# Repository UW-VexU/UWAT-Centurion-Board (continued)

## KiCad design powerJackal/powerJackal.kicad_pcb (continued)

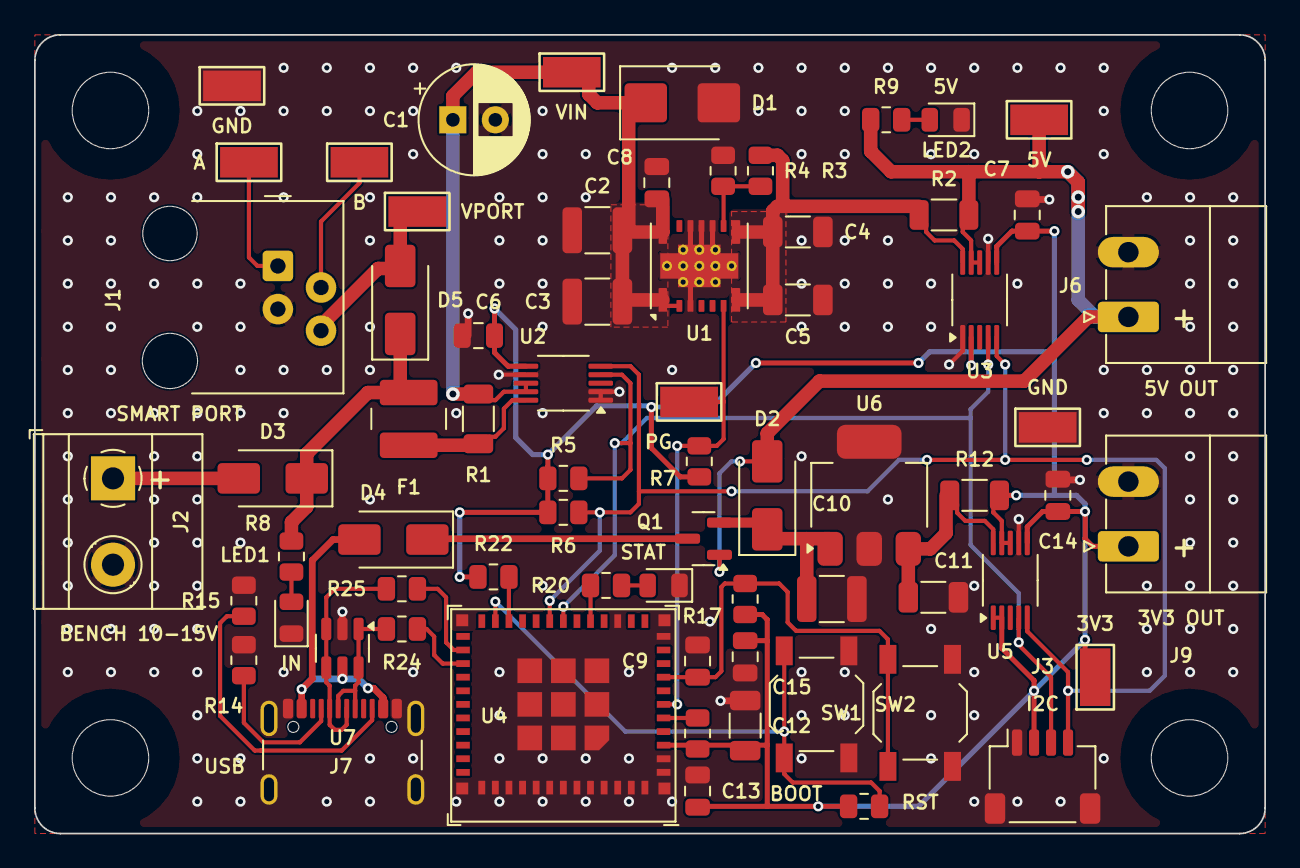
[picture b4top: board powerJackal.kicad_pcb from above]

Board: 2 copper layers, 72.4 x 47.0 mm, 72 parts (0 on the bottom side), 33 nets.

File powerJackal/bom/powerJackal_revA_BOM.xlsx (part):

Smart Port Power Test Board (Jackal), Bill of Materials, Rev A draft 8 (TPSM536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
UWAT VEXU. DigiKey Canada stock and CAD price breaks, read from digikey.ca on O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
Boards to build |  | 5 | Edit the yellow cells. Type your own quantity in the yellow Your order qty colu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
Ref | Block | Description | Manufacturer | Mfr part number | DigiKey part number | Qty per board | Spares | Needed (boards x qty + spares) | Your order qty (optional) | Order qty | Unit price at order qty (CAD) | Order cost (CAD) | Next price break (qty) | Unit price at next break (CAD) | Tip | DigiKey stock | DigiKey Canada link | Notes
J1 | Power input | Smart port jack, 4P4C modular, right angle, through hole | Molex | 0955012441 | WM5568-ND | 1 | 0 | 5 | 10 | 10 | 1.2929999999999999 | 12.93 | 25 | 1.2123999999999999 |  | 4151 | https://www.digikey.ca/en/products/detail/molex/0955012441/1835860 | The board footprint is a placeholder until the Molex drawing is checked. Test-f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
J2 | Power input | Bench supply input, 2-position screw terminal, 5.08 mm | Phoenix Contact | 1935161 | 277-1667-ND | 1 | 0 | 5 | 10 | 10 | 0.64 | 6.4 |  |  |  | 44913 | https://www.digikey.ca/en/products/detail/phoenix-contact/19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 | D3 and D5 OR the two inputs. Either can be plugged in alone or both at once.
D3, D5 | Power input | Input OR diodes, Schottky 40 V 3 A, SMA | Diodes Incorporated | B340A-13-F | B340A-FDICT-ND | 2 | 1 | 11 | 25 | 25 | 0.41239999999999999 | 10.31 | 50 | 0.35899999999999999 |  | 254159 | https://www.digikey.ca/en/products/detail/diodes-incorporate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 | D5 from the smart port, D3 from the bench input.
F1 | Protection | Polyfuse, 1.5 A hold, 3 A trip, 33 V, 2016 SMD | Littelfuse | 2016L150/33DR | 18-2016L150/33DRCT-ND | 1 | 1 | 6 | 10 | 10 | 1.0129999999999999 | 10.129999999999999 | 50 | 0.84060000000000001 |  | 29235 | https://www.digikey.ca/en/products/detail/littelfuse-inc/201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 | Right after the OR diodes.
D1 | Protection | TVS diode, 16 V standoff, about 26 V clamp, unidirectional, SMB | Littelfuse | SMBJ16A | SMBJ16ALFCT-ND | 1 | 1 | 6 | 10 | 10 | 0.48699999999999999 | 4.87 | 50 | 0.35220000000000001 |  | 25785 | https://www.digikey.ca/en/products/detail/littelfuse-inc/SMB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 | Keeps hot-plug spikes well below the TPSM53602's 38 V absolute maximum.
C1 | Protection | Bulk input capacitor, aluminum electrolytic, 47 µF 50 V, 6.3 mm radial, 2.5 mm 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 | Panasonic | EEU-FR1H470 | P124235-ND | 1 | 0 | 5 | 10 | 10 | 0.432 | 4.32 | 50 | 0.31780000000000003 |  | 26276 | https://www.digikey.ca/en/products/detail/panasonic-industry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 | Damps hot-plug ringing and covers the module's bulk input recommendation. Repla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
U1 | 5 V regulator | Step-down power module, 3.8 to 36 V in, 2 A, 1.4 MHz, B3QFN-14 5 x 5.5 mm | Texas Instruments | TPSM53602RDAR | 296-TPSM53602RDARCT-ND | 1 | 0 | 5 | 5 | 5 | 10.72 | 53.6 | 10 | 10.548 |  | 2786 | https://www.digikey.ca/en/products/detail/texas-instruments/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 | Pads under the body: hot plate or hot air with a stencil.
C2, C3, C10 | 5 V regulator | Ceramic capacitor, 10 µF 50 V X7R, 1210 | Samsung Electro-Mechanics | CL32B106KBJNNNE | 1276-3387-1-ND | 3 | 2 | 17 | 25 | 25 | 0.63600000000000001 | 15.9 | 50 | 0.48299999999999998 |  | 742989 | https://www.digikey.ca/en/products/detail/samsung-electro-me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 | C2, C3 at the TPSM53602 input (datasheet asks for 2 x 10 µF). C10 at the LDO in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
C4, C5, C11, C12 | 5 V regulator | Ceramic capacitor, 47 µF 10 V X5R, 1206 | Murata | GRM31CR61A476ME15L | 490-5528-1-ND | 4 | 2 | 22 | 50 | 50 | 0.26679999999999998 | 13.34 | 100 | 0.23719999999999999 |  | 180907 | https://www.digikey.ca/en/products/detail/murata-electronics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 | C4, C5 at the TPSM53602 output (needs 27 µF real at 5 V). C11 at the LDO output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
R4 | 5 V regulator | RFBB, sets 5.0 V out, 2.49 kΩ 1%, 0805 | Yageo | RC0805FR-072K49L | 311-2.49KCRCT-ND | 1 | 2 | 7 | 110 | 110 | 2.87E-2 | 3.157 | 250 | 2.256E-2 |  | 1178164 | https://www.digikey.ca/en/products/detail/yageo/RC0805FR-072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 | With R3 (10 kΩ RFBT), from TPSM53602 datasheet Table 7-1.
U2, U3, U5 | Measurement | Current and voltage monitor, I2C, 0 to 36 V bus, VSSOP-10 | Texas Instruments | INA226AIDGSR | 296-29034-1-ND | 3 | 0 | 15 | 12 | 12 | 3.7770000000000001 | 45.323999999999998 | 25 | 3.4596 |  | 37941 | https://www.digikey.ca/en/products/detail/texas-instruments/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 | U2 input (0x40), U3 5 V rail (0x41), U5 3.3 V rail (0x45).
R1, R2 | Measurement | Current shunt, 20 mΩ 1%, metal strip, 1206 | Vishay Dale | WSL1206R0200FEA | WSLC-.02CT-ND | 2 | 1 | 11 | 25 | 25 | 0.62519999999999998 | 15.629999999999999 | 50 | 0.56159999999999999 |  | 147584 | https://www.digikey.ca/en/products/detail/vishay-dale/WSL120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 | About 4 A full scale on the INA226. Sense traces leave from the inner pad edges.
R12 | Measurement | Current shunt, 50 mΩ 1%, metal strip, 1206 | Vishay Dale | WSL1206R0500FEA | WSLC-.05CT-ND | 1 | 1 | 6 | 12 | 12 | 0.91200000000000003 | 10.944000000000001 | 25 | 0.78520000000000001 |  | 17342 | https://www.digikey.ca/en/products/detail/vishay-dale/WSL120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 | 3.3 V rail shunt. About 1.6 A full scale.
C6 to C8, C13 to C15 | Measurement | Decoupling capacitor, 0.1 µF 50 V X7R, 0805 | Yageo | CC0805KRX7R9BB104 | 311-1140-1-ND | 6 | 2 | 32 | 100 | 100 | 8.8400000000000006E-2 | 8.84 | 500 | 6.5839999999999996E-2 |  | 4955773 | https://www.digikey.ca/en/products/detail/yageo/CC0805KRX7R9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 | C6, C7, C14 at each INA226. C8 at the TPSM53602 input. C13, C15 at the ESP32 3V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
C9 | MCU and USB | Ceramic capacitor, 1 µF 25 V X7R, 0805 | Yageo | CC0805KKX7R8BB105 | 311-1456-1-ND | 1 | 2 | 7 | 20 | 20 | 0.23899999999999999 | 4.7799999999999994 | 50 | 0.1704 |  | 327549 | https://www.digikey.ca/en/products/detail/yageo/CC0805KKX7R8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 | EN delay with R17 (10 kΩ + 1 µF, Espressif's recommended values). Replaces TDK 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
R5, R6 | Measurement | I2C pull-ups, 4.7 kΩ 1%, 0805 | Yageo | RC0805FR-074K7L | 311-4.70KCRCT-ND | 2 | 2 | 12 | 250 | 250 | 2.128E-2 | 5.32 | 500 | 1.7979999999999999E-2 |  | 601787 | https://www.digikey.ca/en/products/detail/yageo/RC0805FR-074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 | To 3.3 V.
J3 | Measurement | STEMMA QT / Qwiic connector, JST SH 4-pin, right angle SMD | JST | SM04B-SRSS-TB | 455-SM04B-SRSS-TBCT-ND | 1 | 0 | 5 | 10 | 10 | 0.64300000000000002 | 6.43 | 100 | 0.54579999999999995 |  | 111721 | https://www.digikey.ca/en/products/detail/jst-sales-america-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 | Spare I2C port (3.3 V, GND, SDA, SCL) for a STEMMA QT display or sensor later.
U6 | 3.3 V regulator | LDO regulator, 3.3 V fixed, 1 A, 250 mV dropout, SOT-223 | Microchip Technology | MCP1826ST-3302E/DB | MCP1826ST-3302E/DBCT-ND | 1 | 1 | 6 | 10 | 10 | 1.44 | 14.399999999999999 | 25 | 1.2192000000000001 |  | 39535 | https://www.digikey.ca/en/products/detail/microchip-technolo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 | Pin 1 IN, 2 GND (tab), 3 OUT, the same as the AP7361C-33E it replaces. That par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
D2, D4 | 3.3 V regulator | Feed diodes, Schottky 40 V 1 A, SMA | Vishay | SS14-E3/61T | SS14-E3/61TGICT-ND | 2 | 1 | 11 | 15 | 15 | 0.42499999999999999 | 6.375 | 50 | 0.30680000000000002 |  | 178712 | https://www.digikey.ca/en/products/detail/vishay-general-sem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 | D2: 5 V rail to the LDO. D4: USB VBUS to the LDO.
U4 | MCU and USB | ESP32-C3 module, RISC-V 160 MHz, 4 MB flash, built-in USB serial/JTAG, U.FL ant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 | Espressif Systems | ESP32-C3-MINI-1U-N4X | 1965-ESP32-C3-MINI-1U-N4XCT-ND | 1 | 0 | 5 | 10 | 10 | 4.6239999999999997 | 46.239999999999995 | 25 | 4.3696000000000002 |  | 4953 | https://www.digikey.ca/en/products/detail/espressif-systems/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 | Recommended chip revision v1.1. Radio not used, so no antenna is fitted. Pads u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
J7 | MCU and USB | USB-C receptacle, USB 2.0, 16 pin, top mount, horizontal | GCT | USB4105-GF-A | 2073-USB4105-GF-ACT-ND | 1 | 1 | 6 | 10 | 10 | 1.004 | 10.039999999999999 | 25 | 0.94079999999999997 |  | 85017 | https://www.digikey.ca/en/products/detail/gct/USB4105-GF-A/11198441 | Flashing and serial over the ESP32-C3's built-in USB, plus backup power for the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

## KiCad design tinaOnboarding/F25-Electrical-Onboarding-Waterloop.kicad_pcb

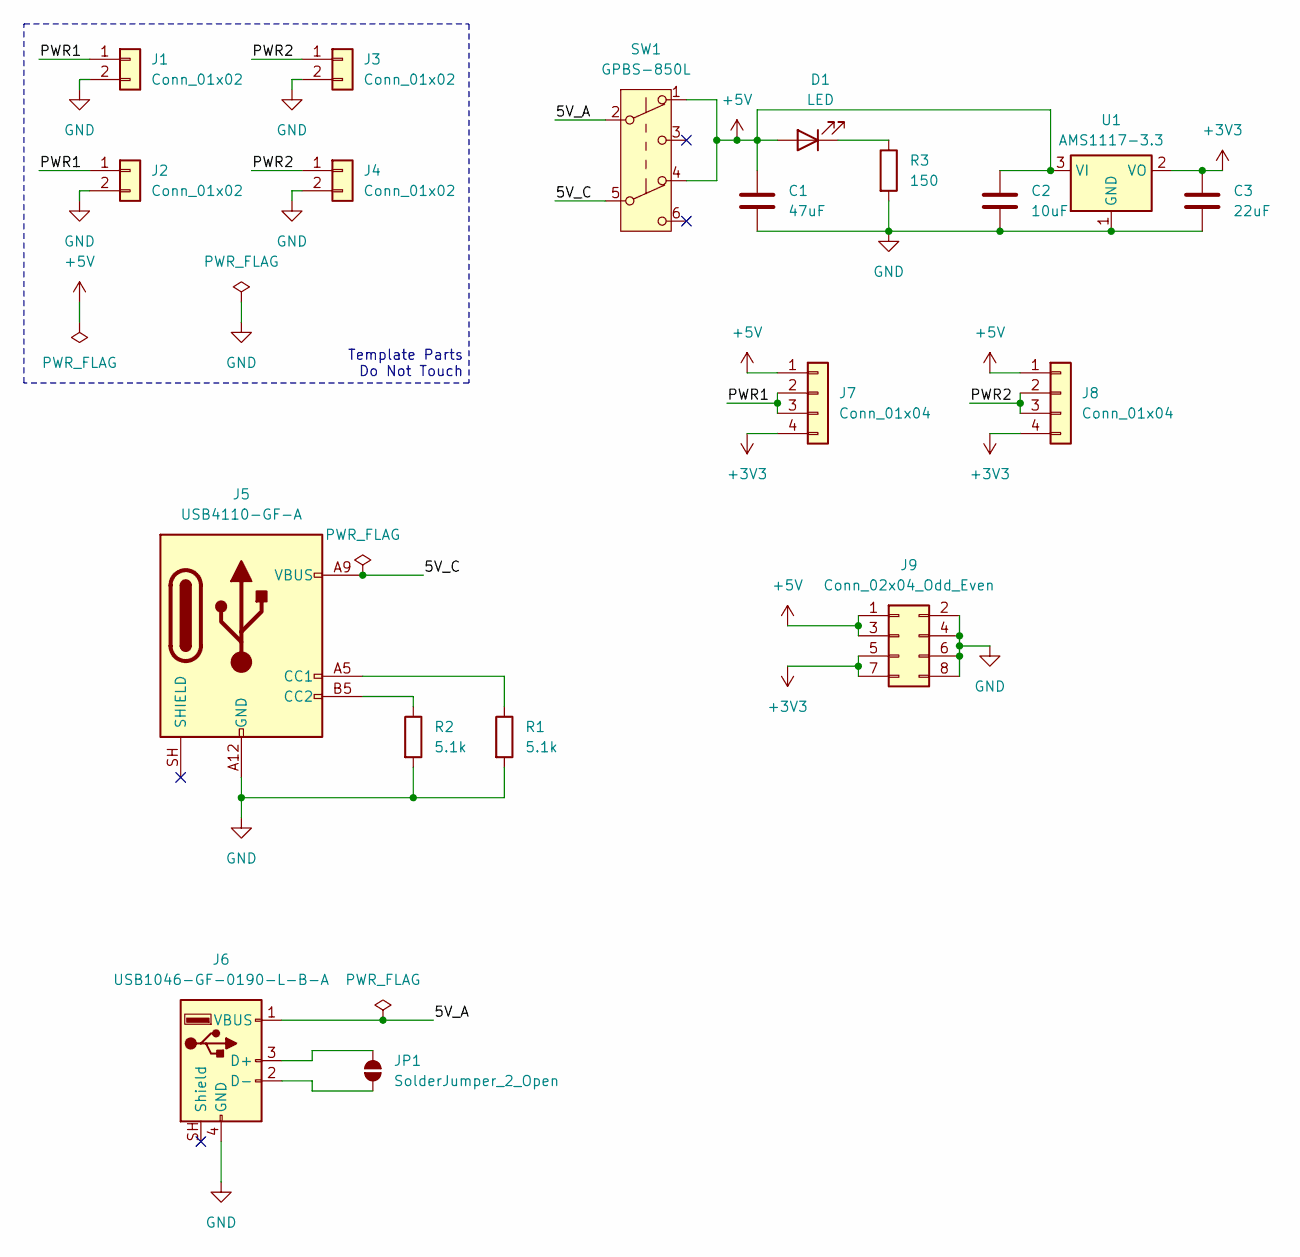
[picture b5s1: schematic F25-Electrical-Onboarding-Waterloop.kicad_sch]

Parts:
C1: 47uF; CP_Radial_D5.0mm_P2.00mm
C2: 10uF; C_0805_2012Metric_Pad1.18x1.45mm_HandSolder
C3: 22uF; C_0805_2012Metric_Pad1.18x1.45mm_HandSolder
D1: LED; LED_0805_2012Metric_Pad1.15x1.40mm_HandSolder
J1, J2, J3, J4: Conn_01x02; PinHeader_1x02_P2.54mm_Vertical
J5: USB4110-GF-A; USB_C_Receptacle_GCT_USB4110
J6: USB1046-GF-0190-L-B-A; USB_A_Receptacle_GCT_USB1046
J7, J8: Conn_01x04; PinHeader_1x04_P2.54mm_Vertical
J9: Conn_02x04_Odd_Even; PinHeader_2x04_P2.54mm_Vertical
JP1: SolderJumper_2_Open; SolderJumper-2_P1.3mm_Open_RoundedPad1.0x1.5mm
R1, R2: 5.1k; R_0805_2012Metric_Pad1.20x1.40mm_HandSolder
R3: 150; R_0805_2012Metric_Pad1.20x1.40mm_HandSolder
SW1: GPBS-850L
U1: AMS1117-3.3; SOT-223-3_TabPin2

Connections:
+3V3: C3.1, J7.4, J8.4, J9.5, J9.7, U1.2 (VO)
+5V: C1.1, C2.1, D1.2 (A), J7.1, J8.1, J9.1, J9.3, SW1.1 (A), SW1.4 (A), U1.3 (VI)
/5V_A: J6.1 (VBUS), SW1.2 (B)
/5V_C: J5.A4 (VBUS), J5.A9 (VBUS), J5.B4 (VBUS), J5.B9 (VBUS), SW1.5 (B)
/PWR1: J1.1, J2.1, J7.2, J7.3
/PWR2: J3.1, J4.1, J8.2, J8.3
GND: C1.2, C2.2, C3.2, J1.2, J2.2, J3.2, J4.2, J5.A1 (GND), J5.A12 (GND), J5.B1 (GND), J5.B12 (GND), J6.4 (GND), J9.2, J9.4, J9.6, J9.8, R1.2, R2.2, R3.2, U1.1 (GND)
unnamed: D1.1 (K), R3.1
unnamed: J5.A5 (CC1), R1.1
unnamed: J5.B5 (CC2), R2.1
unnamed: J6.3 (D+), JP1.1 (A)
unnamed: J6.2 (D-), JP1.2 (B)

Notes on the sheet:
Template Parts Do Not Touch

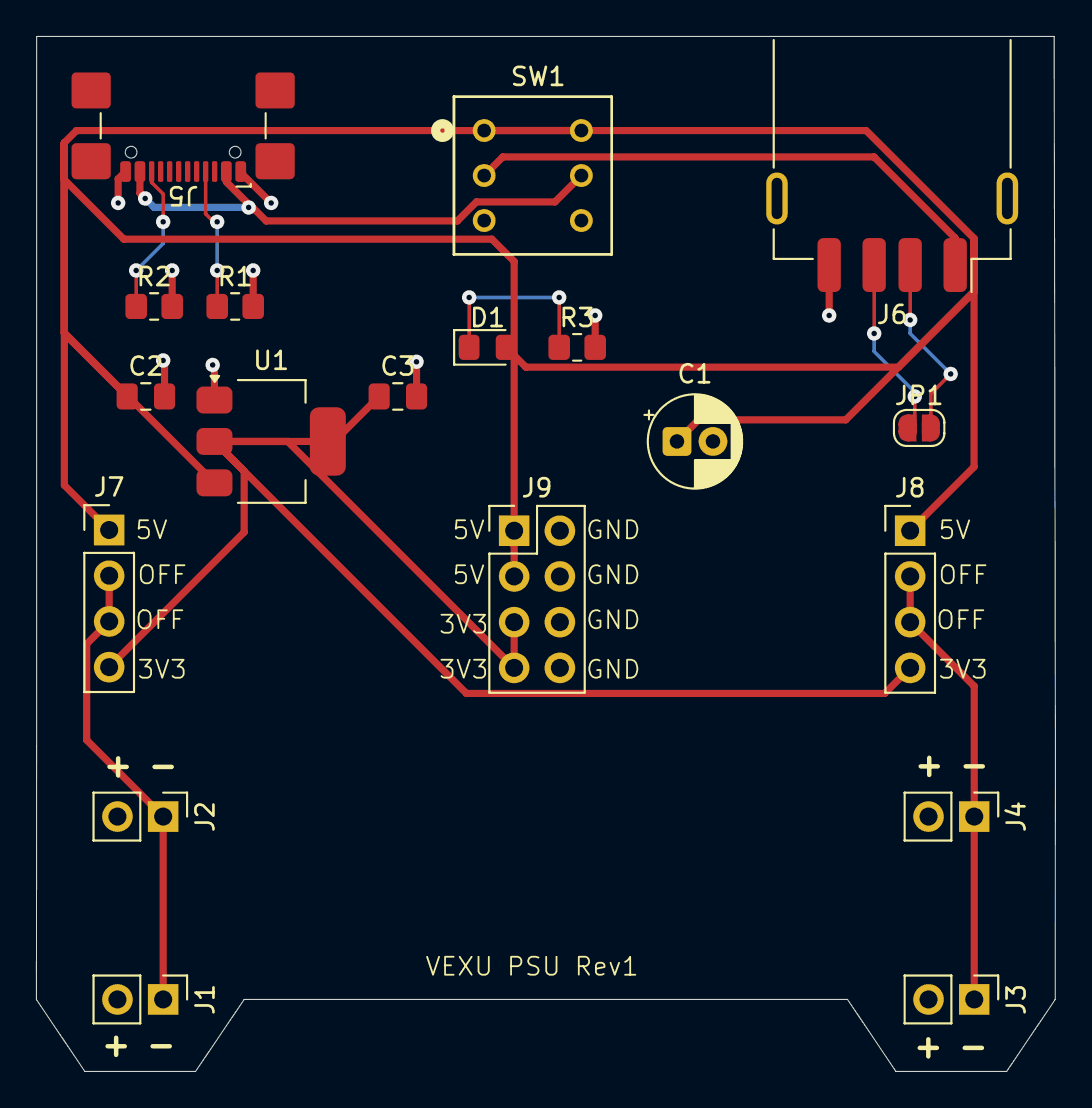
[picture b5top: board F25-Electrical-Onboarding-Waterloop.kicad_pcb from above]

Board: 2 copper layers, 56.6 x 57.5 mm, 19 parts (0 on the bottom side), 12 nets.

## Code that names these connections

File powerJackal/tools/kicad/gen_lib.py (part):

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tp = [pin("power_in", -12.7, 5.08, 0, "VIN", "1"), pin("power_in", -12.7, 5.08, 0, "VIN", "14", hide=True),
      pin("input", -12.7, 0, 0, "EN", "2"),
      pin("power_out", 12.7, 5.08, 180, "VOUT", "7"), pin("power_out", 12.7, 5.08, 180, "VOUT", "8", hide=True),
      pin("input", 12.7, 0, 180, "FB", "9"), pin("open_collector", 12.7, -2.54, 180, "PGOOD", "6"),
      pin("power_out", 12.7, -5.08, 180, "V5V", "13"),
      pin("power_in", 5.08, -15.24, 90, "PGND", "15")] + \
     [pin("power_in", 5.08, -15.24, 90, "NC", n, hide=True) for n in ("3", "10", "11")] + \
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
# ---------- ESP32-C3-MINI-1U (Espressif module, external antenna connector)
ep = [pin("power_in", -19.05, 20.32, 0, "3V3", "3"), pin("input", -19.05, 15.24, 0, "EN", "8"),
      pin("bidirectional", -19.05, 10.16, 0, "GPIO9/BOOT", "23"), pin("bidirectional", -19.05, 7.62, 0, "GPIO8", "22"),
      pin("bidirectional", -19.05, 5.08, 0, "GPIO2", "5"), pin("bidirectional", -19.05, 0, 0, "GPIO0", "12"),
      pin("bidirectional", -19.05, -2.54, 0, "GPIO1", "13")]
for name, num, y in (("GPIO18/USB_D-", "26", 20.32), ("GPIO19/USB_D+", "27", 17.78), ("GPIO20/U0RXD", "30", 12.7),
                     ("GPIO21/U0TXD", "31", 10.16), ("GPIO4", "18", 5.08), ("GPIO5", "19", 2.54), ("GPIO6", "20", 0),
                     ("GPIO7", "21", -2.54), ("GPIO10", "16", -7.62), ("GPIO3", "6", -10.16)):
    ep.append(pin("bidirectional", 19.05, y, 180, name, num))
gnds = ["1", "2", "11", "14"] + [str(n) for n in range(36, 54)]
ep += [pin("power_in", 0, -25.4, 90, "GND", n, hide=i > 0) for i, n in enumerate(gnds)]
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ep += [pin("no_connect", -8.89 + i * 1.27, -17.78, 0, "NC", n, hide=True) for i, n in enumerate(ncs)]
esp = symbol("ESP32-C3-MINI-1U", "U", "ESP32-C3-MINI-1U-N4X", "UWAT:ESP32-C3-MINI-1U",
             "https://documentation.espressif.com/esp32-c3-mini-1_datasheet_en.pdf",
             "ESP32-C3 RISC-V module, 4 MB flash, built-in USB serial/JTAG on GPIO18/19, external antenna connector, 13.2 x 12.5 mm",
             "ESP32-C3 module USB", (-16.51, 22.86, 16.51, -22.86), ep, (-16.51, 24.13), (-16.51, -27.94))

open(os.path.join(OUT, "UWAT.kicad_sym"), "w").write("(kicad_symbol_lib (version 20220914) (generator uwat_gen)\n" + tpsm + esp + ")\n")
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
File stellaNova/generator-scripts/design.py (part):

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j1 = part('stellaNova:V5_SmartPort', 'J1', (124.46, 53.34))
# B line: straight across to J1.2, label part way
s.wire(u3.pin('7'), (93.98, 53.34), j1.pin('2'))
s.label('RS485_B', (93.98, 53.34), (1, 0))
# A line: dog-leg up to J1.1
s.wire(u3.pin('6'), (83.82, 60.96), (83.82, 55.88), (93.98, 55.88), j1.pin('1'))
s.label('RS485_A', (93.98, 55.88), (1, 0))
s.wire(j1.pin('3'), (111.76, 50.8)); s.power(GND, (111.76, 50.8), rot=270)
s.stub(j1, '4', 10.16, to='VBAT_PORT')

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RAIL = 132.08
f1 = part('Device:Polyfuse', 'F1', (31.75, RAIL), rot=90, ref_at=(31.75, RAIL - 3.81), val_at=(31.75, RAIL + 3.81),
          ref_just=None, val_just=None)
s.wire((20.32, RAIL), f1.pin('1')); s.label('VBAT_PORT', (20.32, RAIL), (-1, 0))
d2 = part('Device:D_Schottky', 'D2', (48.26, RAIL), rot=180, ref_at=(48.26, RAIL - 3.81), val_at=(48.26, RAIL + 3.81),
          ref_just=None, val_just=None)
s.wire(f1.pin('2'), d2.pin('2'))
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s.wire(j2.pin('A4'), (365.76, 40.64)); s.power(VBUS, (365.76, 40.64))
s.stub(j2, 'A5', 5.08, to='CC1'); s.stub(j2, 'B5', 2.54, to='CC2')
s.wire(j2.pin('A7'), (363.22, 53.34), (368.3, 53.34)); s.wire(j2.pin('B7'), (363.22, 55.88), (363.22, 53.34))
s.label('USB_DN', (368.3, 53.34), (1, 0))
s.wire(j2.pin('A6'), (363.22, 58.42), (363.22, 60.96), (368.3, 60.96)); s.wire(j2.pin('B6'), (363.22, 60.96))
s.label('USB_DP', (368.3, 60.96), (1, 0))
s.stub(j2, 'A8', nc=True); s.stub(j2, 'B8', nc=True)
s.stub(j2, 'A1', 0, rail=GND); s.stub(j2, 'S1', 0, rail=GND)
r7 = vpass('Device:R', 'R7', 378.46, 66.04, top='CC1', bot=GND)
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
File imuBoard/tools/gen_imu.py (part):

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    dict(ref="J1", lib="Connector_Generic_MountingPin:Conn_01x08_MountingPin", value="BM08B-GHS-TBT",
         fp="Connector_JST:JST_GH_BM08B-GHS-TBT_1x08-1MP_P1.25mm_Vertical", mpn="BM08B-GHS-TBT", mfr="JST",
         desc="To centurion J5: JST GH 8-pin, vertical, straight-through cable",
         pins={"1": "+3V3", "2": "GND", "3": "SCK", "4": "MOSI", "5": "MISO_C", "6": "CS", "7": "INT1", "8": "INT2", "MP": "GND"},
         at=(53.34, 99.06), rot=0, stub={"1": (7.62, (0, -1))}),
    dict(ref="U2", lib="Power_Protection:TPD4E05U06DQA", value="TPD4E05U06DQA",
         fp="imuBoard:TI_DQA_USON-10_2.5x1.0mm_P0.5mm", mpn="TPD4E05U06QDQARQ1", mfr="Texas Instruments",
         desc="4-channel ESD clamp at the cable jack; pins 6, 7, 9 and 10 are not connected inside, the traces run over them (flow-through)",
         pins={"1": "CS", "10": "CS", "2": "SCK", "9": "SCK", "4": "MOSI", "7": "MOSI", "5": "MISO_C", "6": "MISO_C", "3": "GND", "8": "GND"},
         at=(111.76, 99.06), rot=0, fields="below_right"),
    dict(ref="R1", lib="Device:R", value="100", fp="Resistor_SMD:R_0805_2012Metric", mpn="RC0805FR-07100RL", mfr="Yageo",
         desc="MISO series resistor at the IMU: damps the cable (centurion/sim, spi_imu.cir with ROIMU = 140)",
         pins={"1": "MISO_C", "2": "MISO"}, at=(152.4, 78.74), rot=90),
    dict(ref="U1", lib="imuBoard:BMI270", value="BMI270", fp="Package_LGA:Bosch_LGA-14_3x2.5mm_P0.5mm", mpn="BMI270",
         mfr="Bosch Sensortec", desc="6-axis IMU, 4-wire SPI. ASDx, ASCx, OCSB and OSDO are left unconnected (BMI270 datasheet table 25)",
         pins={"1": "MISO", "2": None, "3": None, "4": "INT1", "5": "+3V3", "6": "GND", "7": "GND", "8": "+3V3",
               "9": "INT2", "10": None, "11": None, "12": "CS", "13": "SCK", "14": "MOSI"},
         at=(205.74, 99.06), rot=0),
    dict(ref="C1", lib="Device:C", value="100nF", fp="Capacitor_SMD:C_0805_2012Metric", mpn="CC0805KRX7R9BB104", mfr="Yageo",
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    "SPI mode 0 or 3, 10 MHz max. Centurion has 100 ohm series resistors on SCK, MOSI and CS (R8, R9, R41); R1 here is the matching one on MISO.",
    "BMI270: firmware must upload Bosch's 8 kB config file after every power-up (INIT_CTRL / INIT_DATA), and do one dummy read to select SPI.",
    "Axes as printed on the top silkscreen: +X toward J1, +Y toward H2, +Z up out of the board.",
    "J5 pin 7 (IMU_INT1) is BMI270 INT1 (pin 4); J5 pin 8 (IMU_INT2) is BMI270 INT2 (pin 9).",
]

# =====================================================================================================
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
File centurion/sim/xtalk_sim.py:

import sys, os
sys.path.insert(0, os.path.dirname(os.path.abspath(__file__)))
from run_ngspice import run
D = os.path.join(os.path.dirname(os.path.abspath(__file__)), "xtalk_pair.cir")
def pk(v, base, t, t0=1e-9):
    w = [x - base for tt, x in zip(t, v) if tt > t0]
    return max(w), min(w)
cases = [
 # name, params, victim bias, what matters
 ("MUX_RST <- RS485A_DE, 16.8 mm side by side, mux reset idle on R10 10k (MCU pin not driving)",
  dict(LEN=16.8, KL=0.056, KC=0.039, TR=1.7e-9, DIR=-1, RV1=10e3, CV1=5e-12, CV2=5e-12, VV=3.3)),
 ("MUX_RST <- RS485A_DE, same, MCU pin driving it high",
  dict(LEN=16.8, KL=0.056, KC=0.039, TR=1.7e-9, DIR=-1, RV1=30, CV1=5e-12, CV2=5e-12, VV=3.3)),
 ("MUX_RST <- TOF4_SCL falling, 3.85 mm stacked In2/B.Cu (strong), 10k idle",
  dict(LEN=3.85, KL=0.5, KC=0.5, TR=5e-9, DIR=-1, RDRV=60, CLOAD=10e-12, RV1=10e3, CV1=5e-12, CV2=5e-12, VV=3.3)),
 ("AUX1_SIG (ADC) <- RS485B_TX, 9.3 mm, C31 10 nF at the near end, ADC pin far end",
  dict(LEN=9.3, KL=0.05, KC=0.035, TR=1.7e-9, DIR=1, RV1=6e3, CV1=10e-9, CV2=5e-12, VV=1.0)),
 ("AUX1_SIG (ADC) <- RS485B_TX, same, worst: C31 at the far end, ADC pin near end",
  dict(LEN=9.3, KL=0.05, KC=0.035, TR=1.7e-9, DIR=1, RV1=6e3, CV1=5e-12, CV2=10e-9, RV2=1e9, VV=1.0)),
 ("AUX1_SIG_IN (before R34) <- I2C_AUX_SCL falling, 16 mm, cable side open, R34 10k into C31",
  dict(LEN=16.0, KL=0.046, KC=0.032, TR=5e-9, DIR=-1, RDRV=60, RV1=10e3, CV1=15e-12, CV2=10e-12, VV=1.0)),
 ("RS485A_RX <- RS485A_TX, 11.3 mm, RX driven by the MAX33071E (about 50 ohm)",
  dict(LEN=11.3, KL=0.068, KC=0.048, TR=1.7e-9, DIR=1, RV1=50, CV1=5e-12, CV2=5e-12, VV=3.3)),
 ("IMU_INT2 <- SWDIO, 3.6 mm (SWD only while debugging), INT2 driven by the IMU",
  dict(LEN=3.6, KL=0.067, KC=0.047, TR=1.7e-9, DIR=1, RV1=100, CV1=5e-12, CV2=5e-12, VV=3.3)),
]
for name, p in cases:
    v = run(D, **{k: (repr(x)) for k, x in p.items()})
    t = v["time"]; base = p.get("VV", 3.3)
    hi0, lo0 = pk(v["v0"], base, t); hi1, lo1 = pk(v["v10"], base, t)
    print("%-95s near %+7.1f/%+7.1f mV  far %+7.1f/%+7.1f mV" % (name, hi0 * 1e3, lo0 * 1e3, hi1 * 1e3, lo1 * 1e3))

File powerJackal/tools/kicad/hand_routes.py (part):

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
# ======================================================================= inputs: J1, D5, TP1, D3, F1, R1 / U2
remove_in_box(["VPORT"], (15.0, 9.0, 24.0, 18.5))
path("VPORT", [(16.54, 17.41), (20.2, 13.75), (21.5, 13.75)], 0.8)                     # off J1's round pin at 45, straight into D5.2
path("VPORT", [(21.5, 13.6), (21.5, 10.4)], 0.8)                                       # D5.2 straight up into TP1
remove_in_box(["VIN_OR"], (14.0, 16.0, 24.0, 27.0))
path("VIN_OR", [(21.5, 17.6), (21.5, 21.05)], 0.8)                                     # D5.1 straight down into F1.1
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remove_in_box(["VIN_MOD"], (31.5, 1.0, 38.5, 17.0))
path("VIN_MOD", [(31.6, 2.2), (32.6, 2.2), (32.6, 3.5), (33.1, 4.0), (35.95, 4.0)], 0.8)   # TP2 down, 45, straight into D1.1
path("VIN_MOD", [(34.95, 4.0), (34.95, 11.5)], 0.8)                                       # D1.1 straight down into C2.1
path("VIN_MOD", [(34.575, 11.6), (36.955, 11.6)], 0.8)                                    # C2.1 straight into VIN (pin 14)
path("VIN_MOD", [(36.955, 9.65), (36.955, 11.6)], 0.8)                                    # C8.1 straight down into pin 14
path("VIN_MOD", [(34.575, 11.5), (34.575, 15.7)], 0.8)                                    # C2.1 to C3.1
path("VIN_MOD", [(34.575, 15.6), (36.955, 15.6)], 0.8)                                    # C3.1 straight into VIN (pin 1)
path("VIN_MOD", [(37.93, 15.95), (36.955, 15.95)], 0.25)                                  # pin 2 to pin 1
move_fp("R3", 42.7, 8.0); move_fp("R4", 40.5, 8.0)                                        # 0.5 mm up so the 5V_MOD run clears R3.2
remove_in_box(["5V_MOD"], (41.0, 7.0, 44.5, 16.0))
path("5V_MOD", [(41.43, 11.6), (43.425, 11.6)], 0.8)                                     # VOUT pin 8 straight into C4.1
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remove_in_box(["PGOOD"], (35.5, 24.5, 39.0, 39.6), layer="B.Cu")
move_via("PGOOD", (36.086, 39.4), (37.8, 39.4)); remove_seg("PGOOD", (37.0, 39.4), (36.086, 39.4))
path("PGOOD", [(37.8, 24.188), (37.8, 39.4)], 0.25, layer="B.Cu")
path("PGOOD", [(37.0, 39.4), (37.8, 39.4)], 0.25)                                           # pin 6 straight out to its via

# ======================================================================= ESP32-C3: support parts lined up with the pins they serve
move_fp("R22", 26.988, 31.9); move_fp("R20", 33.612, 32.4); move_fp("LED3", 37.0, 32.4)
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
